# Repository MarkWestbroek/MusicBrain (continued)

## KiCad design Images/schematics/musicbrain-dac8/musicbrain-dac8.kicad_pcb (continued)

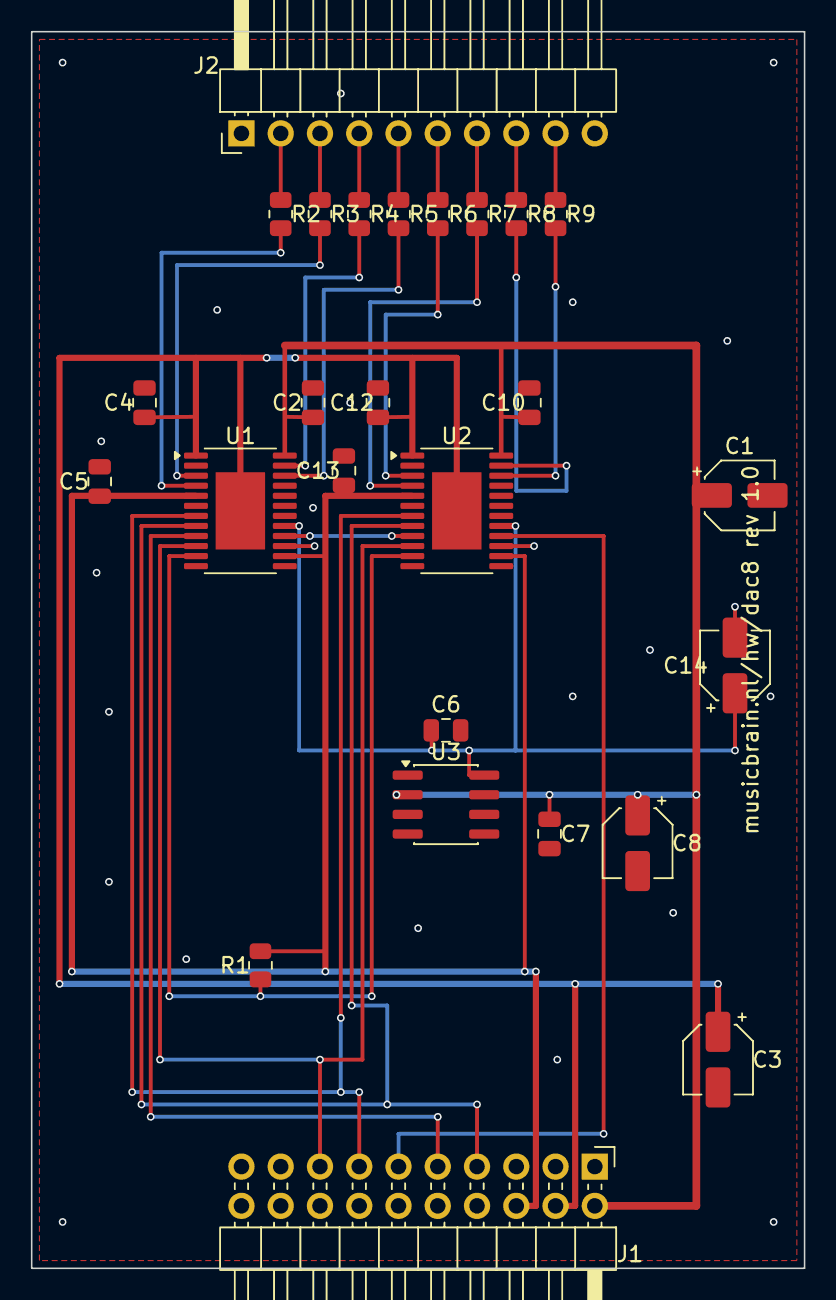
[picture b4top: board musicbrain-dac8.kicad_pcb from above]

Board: 2 copper layers, 50.0 x 80.0 mm, 26 parts (0 on the bottom side), 28 nets.

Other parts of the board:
C14: 10u; CP_Elec_4x5.3

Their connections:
/VREF: C14.1; also elsewhere on the board
GND: C14.2; also elsewhere on the board

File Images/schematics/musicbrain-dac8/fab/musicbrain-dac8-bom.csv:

"Comment","Designator","Footprint","Qty","LCSC Part #"
"10u","C1,C3,C8,C14","Capacitor_SMD:CP_Elec_4x5.3","4",""
"100n","C2,C4-C7,C10,C12,C13","Capacitor_SMD:C_0805_2012Metric","8",""
"BUS","J1","Connector_PinHeader_2.54mm:PinHeader_2x10_P2.54mm_Horizontal","1",""
"CV OUT","J2","Connector_PinHeader_2.54mm:PinHeader_1x10_P2.54mm_Horizontal","1",""
"10k","R1","Resistor_SMD:R_0805_2012Metric","1",""
"100R","R2-R9","Resistor_SMD:R_0805_2012Metric","8",""
"AD5754BREZ","U1,U2","Package_SO:HTSSOP-24-1EP_4.4x7.8mm_P0.65mm_EP3.2x5mm","2",""
"ADR421","U3","Package_SO:SOIC-8_3.9x4.9mm_P1.27mm","1",""

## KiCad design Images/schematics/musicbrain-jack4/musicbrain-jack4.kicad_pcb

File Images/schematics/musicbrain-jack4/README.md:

# MusicBrain jack4 — Thonkiconn-paneeldrager (8 jacks)

**Status**: schema ERC-schoon; PCB volledig geroute (DRC 0/0). Bord 20×65 mm.
**Zusje: `musicbrain-jack8/` (8 jacks + 1×10 header).**

## Wat het is

Een passieve strip met **4× Thonkiconn** (PJ398SM = PJ301M-12 = WQP518MA,
onderling uitwisselbaar) op 15 mm steek, die als **frontpaneel-drager**
dient: de schroefbussen steken door het paneel en de moeren klemmen paneel
en printje op elkaar — geen extra steunen nodig.

## Aansluiting op de kaarten

- **J1** (1×6): 1 = GND, 2–5 = CH1..4, 6 = GND — hetzelfde contract als
  J2 op GATE8 én ADC8, dus één jack4 past op beide kaartsoorten.
- **Montage**: de female socket wordt op de **achterzijde** gesoldeerd
  (opening richting kaart); de kaart krijgt aan zijn frontrand een haakse
  male header. Het silkscreen op de achterzijde markeert de positie.
- Headerpositie: hart op **44 mm boven de onderrand** — de
  standaard-fronthoogte uit `doc/spi-bus-spec.md`, zodat elk jack-printje
  op elke kaart past.

## JP1: schakelcontact-normalling

Elke Thonkiconn heeft een schakelcontact (TN) dat bij een ongepatchte jack
tegen de tip ligt. Alle TN's zijn gebust naar één soldeerjumper **JP1**:

- **INPUT-kaart (ADC8): JP1 dichtsolderen** → ongepatchte ingangen lezen
  netjes 0 V.
- **OUTPUT-kaart (GATE8/DAC): JP1 OPEN laten!** Anders wordt elke
  ongepatchte uitgang via het schakelcontact naar GND kortgesloten
  (de 100R/1k serieweerstanden beperken dat, maar het hoort niet).

## Paneel

3U Eurorack: paneelhoogte 128,5 mm; boorpatroon = 4× Ø6 mm gat op 15 mm
steek, gecentreerd op de jackposities (eerste jack 8 mm van de bovenrand
van het printje). Printje zelf is 65 mm hoog (half 3U-paneel of 3U half gevuld).

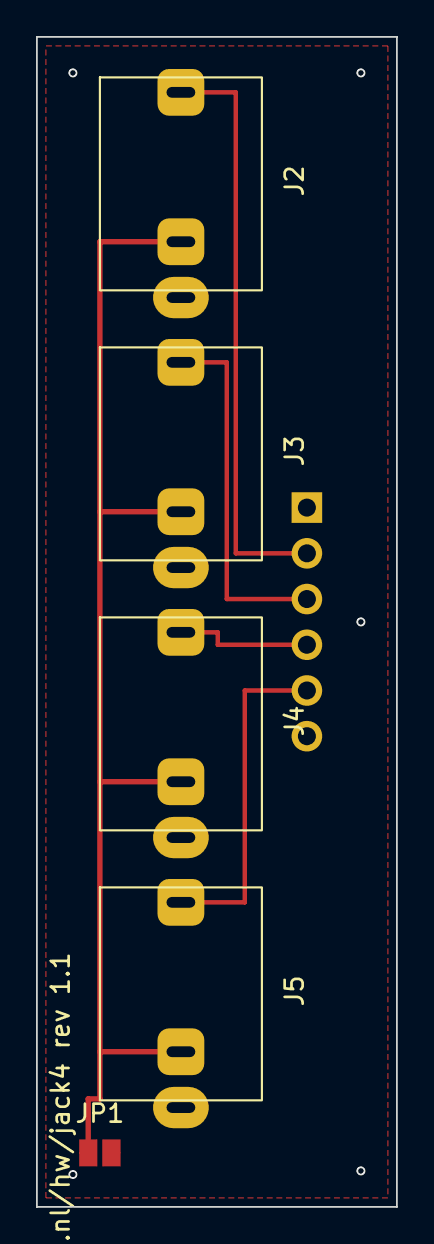
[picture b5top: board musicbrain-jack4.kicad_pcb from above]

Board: 2 copper layers, 20.0 x 65.0 mm, 6 parts (1 on the bottom side), 6 nets.

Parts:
J1: SOCKET-BACK; Header_1x06_backside
J2, J3, J4, J5: PJ398SM; Jack_3.5mm_PJ398SM_Thonkiconn
JP1: NORM=GND; SolderJumper-2_P1.3mm_Open_TrianglePad1.0x1.5mm

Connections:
/CH1: J1.2, J2.1
/CH2: J1.3, J3.1
/CH3: J1.4, J4.1
/CH4: J1.5, J5.1
/NORM: J2.3, J3.3, J4.3, J5.3, JP1.1
GND: J1.1, J1.6, J2.2, J3.2, J4.2, J5.2, JP1.2

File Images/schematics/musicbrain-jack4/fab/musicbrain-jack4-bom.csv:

"Comment","Designator","Footprint","Qty","LCSC Part #"
"NAAR KAART","J1","Connector_PinSocket_2.54mm:PinSocket_1x06_P2.54mm_Vertical","1",""
"PJ398SM","J2-J5","MusicBrain:Jack_3.5mm_PJ398SM_Thonkiconn","4",""
"NORM=GND (dicht voor inputs)","JP1","Jumper:SolderJumper-2_P1.3mm_Open_TrianglePad1.0x1.5mm","1",""

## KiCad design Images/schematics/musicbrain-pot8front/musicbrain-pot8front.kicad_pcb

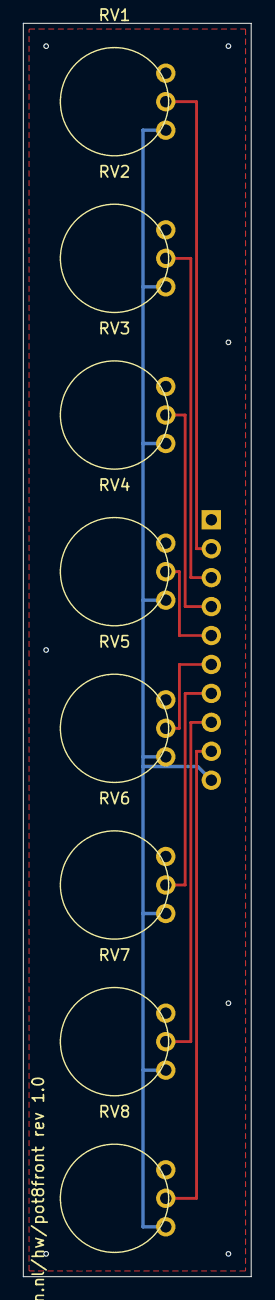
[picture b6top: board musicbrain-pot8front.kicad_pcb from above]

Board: 2 copper layers, 20.0 x 110.0 mm, 9 parts (1 on the bottom side), 10 nets.

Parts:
J1: SOCKET-BACK; Socket_1x10_backside
RV1, RV2, RV3, RV4, RV5, RV6, RV7, RV8: RK097N 10k; RK097N_Vertical

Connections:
+3V3: J1.10, RV1.3, RV2.3, RV3.3, RV4.3, RV5.3, RV6.3, RV7.3, RV8.3
/W1: J1.2, RV1.2
/W2: J1.3, RV2.2
/W3: J1.4, RV3.2
/W4: J1.5, RV4.2
/W5: J1.6, RV5.2
/W6: J1.7, RV6.2
/W7: J1.8, RV7.2
/W8: J1.9, RV8.2
GND: J1.1, RV1.1, RV2.1, RV3.1, RV4.1, RV5.1, RV6.1, RV7.1, RV8.1

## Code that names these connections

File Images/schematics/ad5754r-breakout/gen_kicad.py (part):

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# ── AD5754BREZ TSSOP-24 Pinout (from datasheet Table 5) ────────────────
# Pin  1: AVSS       - Negative analog supply (-12V)
# Pin  2: NC         - No connect
# Pin  3: VOUTA      - DAC A output
# Pin  4: VOUTB      - DAC B output
# Pin  5: BIN/2sCOMP - Coding select (GND = twos complement)
# Pin  6: NC         - No connect
# Pin  7: SYNC       - SPI CS (active low)
# Pin  8: SCLK       - SPI clock
# Pin  9: SDIN       - SPI data in
# Pin 10: LDAC       - Load DAC (GND = immediate update)
# Pin 11: CLR        - Clear (active low, -> DVCC via 10k)
# Pin 12: NC         - No connect
# Pin 13: NC         - No connect
# Pin 14: DVCC       - Digital supply (+3.3V)
# Pin 15: GND        - Ground reference
# Pin 16: SDO        - SPI data out
# Pin 17: REFIN      - External reference input (ADR421 VOUT -> here)
# Pin 18: DAC_GND   - DAC ground
# Pin 19: DAC_GND   - DAC ground
# Pin 20: SIG_GND   - Output amplifier ground
# Pin 21: SIG_GND   - Output amplifier ground
# Pin 22: VOUTD      - DAC D output
# Pin 23: VOUTC      - DAC C output
# Pin 24: AVDD       - Positive analog supply (+12V)
# Exposed paddle: AVSS (thermally connect to copper plane)

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    # Left side pins (1-12)
    pin("power_in",  "line", "-10.16 14.28",  "2.54", "AVSS",      "1",  angle="0")
    pin("no_connect","line", "-10.16 11.74",  "2.54", "NC",        "2",  angle="0", hide_name=True)
    pin("output",    "line", "-10.16 9.20",   "2.54", "VOUTA",     "3",  angle="0")
    pin("output",    "line", "-10.16 6.66",   "2.54", "VOUTB",     "4",  angle="0")
    pin("input",     "line", "-10.16 4.12",   "2.54", "BIN/2sCOMP","5",  angle="0")
    pin("no_connect","line", "-10.16 1.58",   "2.54", "NC",        "6",  angle="0", hide_name=True)
    pin("input",     "line", "-10.16 -1.02",  "2.54", "SYNC",      "7",  angle="0")
    pin("input",     "line", "-10.16 -3.56",  "2.54", "SCLK",      "8",  angle="0")
    pin("input",     "line", "-10.16 -6.10",  "2.54", "SDIN",      "9",  angle="0")
    pin("input",     "line", "-10.16 -8.64",  "2.54", "LDAC",      "10", angle="0")
    pin("input",     "line", "-10.16 -11.18", "2.54", "CLR",       "11", angle="0")
    pin("no_connect","line", "-10.16 -13.72", "2.54", "NC",        "12", angle="0", hide_name=True)
    # Right side pins (13-24)
    pin("no_connect","line", "10.16 -13.72",  "2.54", "NC",        "13", angle="180", hide_name=True)
    pin("power_in",  "line", "10.16 -11.18",  "2.54", "DVCC",      "14", angle="180")
    pin("power_in",  "line", "10.16 -8.64",   "2.54", "GND",       "15", angle="180")
    pin("output",    "line", "10.16 -6.10",   "2.54", "SDO",       "16", angle="180")
    pin("input",     "line", "10.16 -3.56",   "2.54", "REFIN",     "17", angle="180")
    pin("power_in",  "line", "10.16 -1.02",   "2.54", "DAC_GND",   "18", angle="180")
    pin("power_in",  "line", "10.16 1.58",    "2.54", "DAC_GND",   "19", angle="180")
    pin("power_in",  "line", "10.16 4.12",    "2.54", "SIG_GND",   "20", angle="180")
    pin("power_in",  "line", "10.16 6.66",    "2.54", "SIG_GND",   "21", angle="180")
    pin("output",    "line", "10.16 9.20",    "2.54", "VOUTD",     "22", angle="180")
    pin("output",    "line", "10.16 11.74",   "2.54", "VOUTC",     "23", angle="180")
    pin("power_in",  "line", "10.16 14.28",   "2.54", "AVDD",      "24", angle="180")
    c()
    c()
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
    # ── Net labels ──
    r('(label "SCLK" (at 55 80 0) (effects (font (size 1.27 1.27)) (justify left)))')
    r('(label "SDIN" (at 55 85 0) (effects (font (size 1.27 1.27)) (justify left)))')
    r('(label "SDO" (at 55 90 0) (effects (font (size 1.27 1.27)) (justify left)))')
    r('(label "SYNC" (at 55 95 0) (effects (font (size 1.27 1.27)) (justify left)))')
    r('(label "VOUTA" (at 55 40 0) (effects (font (size 1.27 1.27)) (justify left)))')
    r('(label "VOUTB" (at 55 45 0) (effects (font (size 1.27 1.27)) (justify left)))')
    r('(label "VOUTC" (at 55 50 0) (effects (font (size 1.27 1.27)) (justify left)))')
    r('(label "VOUTD" (at 55 55 0) (effects (font (size 1.27 1.27)) (justify left)))')
    r('(label "REFIN" (at 130 40 0) (effects (font (size 1.27 1.27)) (justify left)))')

    # ── U1 — AD5754BREZ ──
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    c()

    # ── Resistors ──
    # R1 — 10k CLR pull-up (pin 11 -> DVCC)
    sym("Device:R", "95 60 90")
    r("(in_bom yes) (on_board yes) (uuid \"mb000003-0001-0001-0001-00000000000e\")")
    prop("Reference", "R1", "95 57 0")
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    prop("Footprint", "Resistor_SMD:R_0805_2012Metric", "0 0 0", hide=True)
    c()

    # ── LDAC -> GND (pin 10) ──
    sym("power:GND", "95 70 0")
    r("(in_bom yes) (on_board yes) (uuid \"mb000003-0001-0001-0001-000000000014\")")
    prop("Reference", "#PWR07", "95 70 0", hide=True)
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    r('(text "AD5754BREZ Minimal DAC Breakout" (at 30 30 0)\n    (effects (font (size 2.54 2.54) bold) (justify left)))')
    r('(text "Quad 16-bit DAC - Bipolar +/-5V mode\\nTSSOP-24 package, SPI interface\\nAD5754BREZ (non-R, no internal ref)\\nDesigned for JLCPCB PCBA assembly" (at 30 35 0)\n    (effects (font (size 1.27 1.27)) (justify left)))')
    r('(text "Power:\\n  AVDD = +12V (Eurorack)\\n  AVSS = -12V (Eurorack)\\n  DVCC = +3.3V (Teensy)\\n  All GND/DAC_GND/SIG_GND to unified ground plane\\n  Exposed paddle = AVSS (thermal)" (at 30 120 0)\n    (effects (font (size 1.016 1.016)) (justify left)))')
    r('(text "SPI (Teensy 4.1):\\n  SCLK  -> Pin 13 (SCK)\\n  SDIN  -> Pin 11 (MOSI)\\n  SDO   -> Pin 12 (MISO)\\n  SYNC  -> Pin 10 (CS)\\n  SPI Mode 1 (CPOL=0, CPHA=1)" (at 30 135 0)\n    (effects (font (size 1.016 1.016)) (justify left)))')
    r('(text "Control pins:\\n  LDAC -> GND (immediate update)\\n  CLR  -> DVCC via 10k (no accidental clear)\\n  BIN/2sCOMP -> GND (twos complement coding)\\n  NC pins 2,6,12,13: leave unconnected" (at 100 120 0)\n    (effects (font (size 1.016 1.016)) (justify left)))')
    r('(text "Outputs:\\n  VOUTA-D -> 100R series -> header\\n  (short-circuit protection)\\n  +/-5V bipolar range (software config)\\n  0x0000=-5V, 0x8000=0V, 0xFFFF=+5V" (at 100 135 0)\n    (effects (font (size 1.016 1.016)) (justify left)))')
    r('(text "ADR421 Reference (MANDATORY):\\n  AD5754BREZ has NO internal reference\\n  ADR421 provides 2.5V ultra-precision (3 ppm/C)\\n  VOUT -> REFIN pin 17\\n  Cannot omit U2 on this chip variant!" (at 100 150 0)\n    (effects (font (size 1.016 1.016)) (justify left)))')
    r('(text "NOTE: This is the AD5754BREZ (TSSOP-24)\\nNOT the AD5754R (SSOP-28). Pinout is\\ndifferent! See datasheet Table 5.\\nNo RSET, no DCEN, no BIN/OFF pin." (at 30 155 0)\n    (effects (font (size 1.016 1.016) bold) (justify left)))')
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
